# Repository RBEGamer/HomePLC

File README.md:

HomePLC is a PLC for smarthome purposes, to control your lamps, devices or machines. 
You can use as input several sensors or webservices. For the HomePLC you will need at least the main unit. 
The main unit contains a RaspberryPi witch run the HomePLC-Server software.
As connection to the modules (like relais, sensors,..), it uses a standard USB2RS485 stick.
To connect the Mainunit to the modules it uses a 4 wire standard cable, which contains power and serial data. 
The Serial data bus is RS485@9600 but you can change it to our needs.

# Features:
* RaspberryPi and Arduino based hardware
* PLC oriented programming node based programming language
* Simple Programming Interface
* Arduino Based Hardware Extentions (DMX, Relais, SensorInterfaces, Analog Inputs, GPS, RTC, RS485, PWM-Output,...)
* Webservice integration (OpenWeatherMap,Philips Hue, Netatmo)
* Din Rail Case for integration into exisitng PLC Systems
* Debug webserver at port 5555
* LUA scripting integration to create complex control flows and create your own programming nodes
* Simple Full-Duplex RS485 Protocol to connect further hardware
* Actor and sensor can be combined in one module

# HARDWARE (MAIN UNIT)
* Linux based computer, to mount it at the DIN-Rail i used a RaspberryPi 3
* 5V and 12V switching power supply (search for combined)
* Arduino Micro (for controlling system status: LED, LCD, POWER)
* I2C 16x2 Display for status information
* 3 LEDs for power, error and message signals
* Sub-D9 female connector to connect modules
* 2 USB2Serial converter, if your linux board have no gpio based serial port 
* RS485 transceiver chip [optional isolated]
* DIN-Rail case

# HARDWARE 4-DO (SAMPLE MODULE)
* Din-Rail case
* 2 state leds [optional]
* Arduino micro
* RS485 transceiver chip [optional isolated]
* 2 Sub-D9 female connectors [in/out]
* 4 channel relais board

# SOFTWARE
The software are splitted in two parts :
* HomePLC-Server (runs on your main unit to control your devices, this repo)
* HomePLC-Commander (Design the interaction beween the modules and create the schematic files and upload it to your main unit)

### The HomePLC_Commander software was moved to [HomePLC_Commander](https://github.com/RBEGamer/HomePLC_Commander)

###  SCHEMATIC

###  NODE PARAMETER EDITOR

The HomePLC schematic is a grafical control language (like FUP) to design the control logic.
You have several nodes like standard logical operations :
* AND, OR, NOT,...
* FLIPFLOS
* MATH
* CONSTANS
* Time/r Nodes
* Compares
* Serial IN/OUT
* TCP/UDP IN/OUT
* DMX send

All other currently implemented nodes are located at:
`./Documentation/Implmented Nodes.csv`

If you have designed a schematic, enter the ip to upload a xml design file to the HomePLC-MainUnit.
The main unit will restart and will start to execute the new schematic. 
You can see the process and errors over the debug interfache.

# LOCATIONS
* A debug build of the HomePLC-Server for the RaspberryPi3 is located at `/Source/BUILDS/BUILD_15_01_2016/`
* The source of the HomePLC-Server to build ith on your own system is located at `./Source/SmartSPS/`
* The HomePLC-Commander source is located at `./Source/SmartPLC_Commander/`
* Sample programs for the HomePLC-Commander are located at `./Documentation/SampleConfig/for_smartsps_commander/`
* Pictures of the MainUnit hardware are located at `./Documentation/Pictures/`

# TODO
* Add MODBUS-TCP
* Add realtime node debugging
* Add cmakelists

# IMAGES
###  BASE MAIN UNIT

### TWO EXTENTIONS (left 6 channel relais, right, 12 channel analog input)

### OPEN MAIN UNIT

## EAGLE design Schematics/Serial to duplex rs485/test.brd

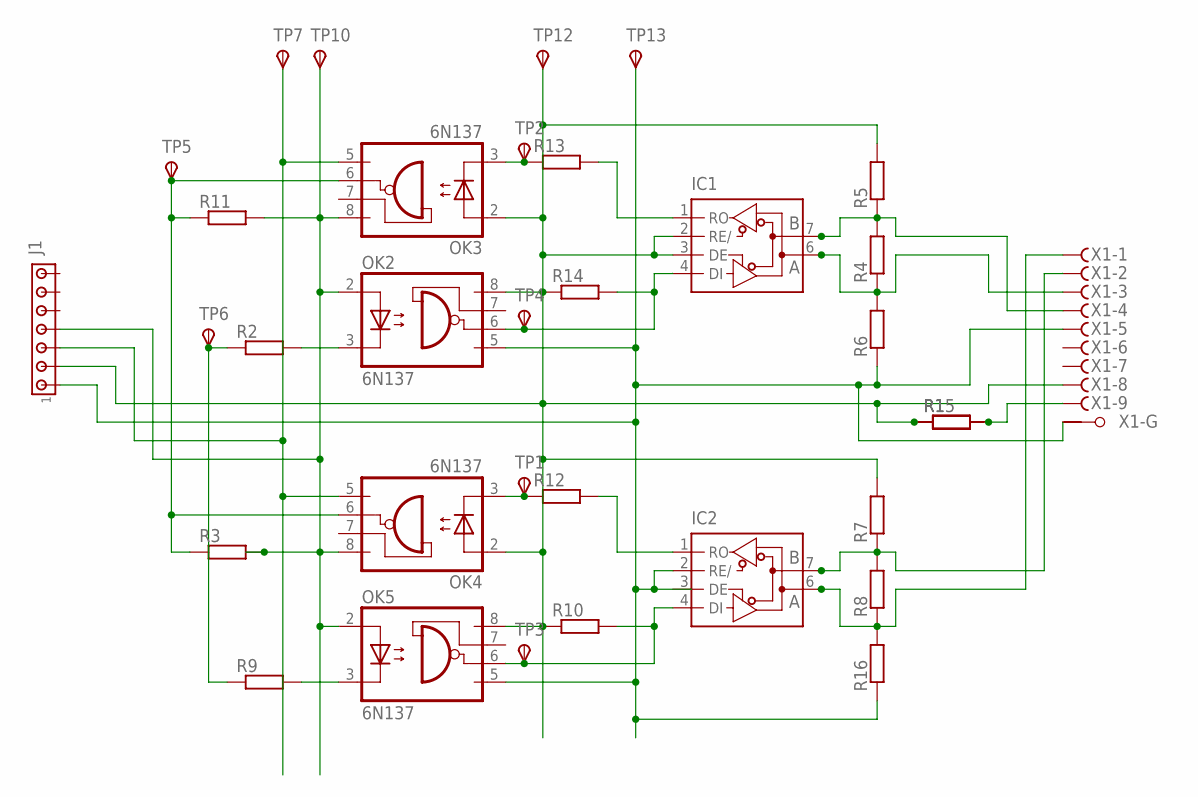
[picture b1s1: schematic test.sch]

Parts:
IC1, IC2: MAX481CSA; SO08
J1: MTA07-100; 10X07MTA
OK2, OK3, OK4, OK5: 6N137; DIL08
R1, R2, R3, R4, R5, R6, R7, R8, R9, R10, R11, R12, R13, R14, R15, R16: SMK
TP1, TP2, TP3, TP4, TP5, TP6, TP7, TP10, TP12, TP13: TPSB2,54; B2,54
X1: F09HPS; F09HP

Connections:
5VEXT: IC1.2 (RE/), IC1.3 (DE), J1.2, OK2.8 (VCC), OK3.2 (A), OK4.2 (A), OK5.8 (VCC), R1.2, R5.1, R7.1, R10.2, R14.2, R15.2, TP12.TP, X1.8 (F)
GND: IC1.5 (GND), IC2.5 (GND)
unnamed: IC1.7 (B), R4.1, R5.2, X1.4 (F)
unnamed: IC1.6 (A), R4.2, R6.1, X1.3 (F)
unnamed: IC2.7 (B), R7.2, R8.1, X1.2 (F)
unnamed: IC2.6 (A), R8.2, R16.1, X1.1 (F)
unnamed: OK3.3 (C), R13.2, TP2.TP
unnamed: IC1.1 (RO), R13.1
unnamed: OK5.3 (C), R9.1
unnamed: OK4.3 (C), R12.2, TP1.TP
unnamed: J1.3, OK3.5 (GND), OK4.5 (GND), TP7.TP
unnamed: R1.1, R15.1, X1.9 (F)
unnamed: IC2.4 (DI), OK5.6 (VO), R10.1, TP3.TP
unnamed: IC1.4 (DI), OK2.6 (VO), R14.1, TP4.TP
unnamed: OK2.3 (C), R2.1
unnamed: IC2.2 (RE/), J1.1, OK2.5 (GND), OK5.5 (GND), R6.2, R16.2, TP13.TP, X1.5 (F), X1.G1
unnamed: J1.4, OK2.2 (A), OK3.8 (VCC), OK4.8 (VCC), OK5.2 (A), R3.1, R11.1, TP10.TP
unnamed: R2.2, R9.2, TP6.TP
unnamed: OK3.6 (VO), OK4.6 (VO), R3.2, R11.2, TP5.TP
unnamed: IC2.1 (RO), R12.1
VCC: IC1.8 (VCC), IC2.8 (VCC)

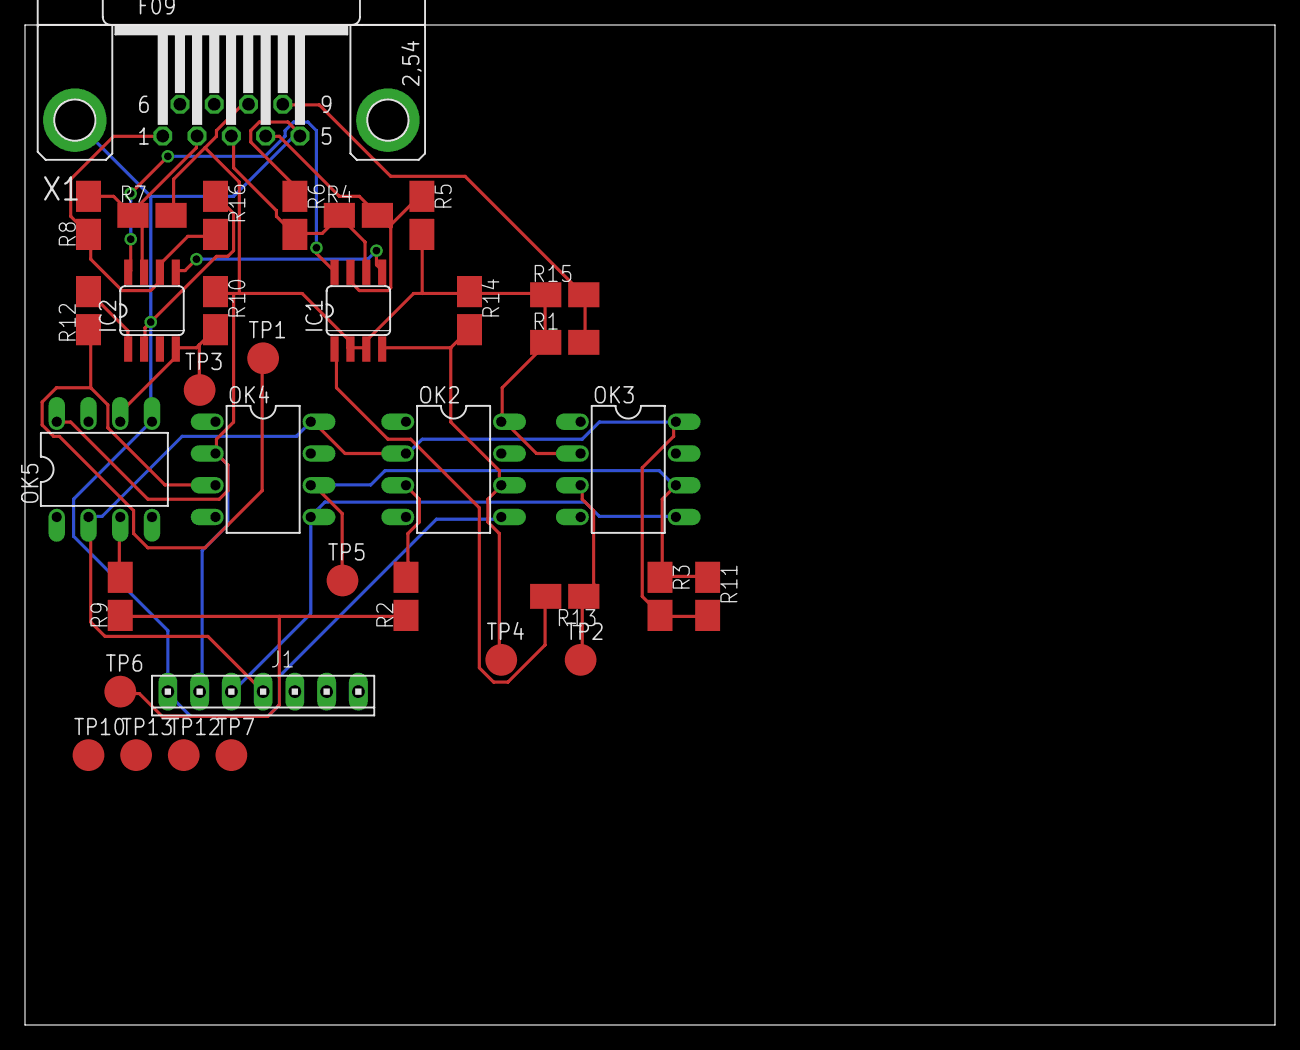
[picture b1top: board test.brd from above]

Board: 2 copper layers, 100.0 x 80.0 mm, 34 parts (0 on the bottom side), 21 nets.

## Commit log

2015-12-06 added some project files
2015-12-06 added 3d print files
2015-12-07 add all nodes from 06.12 to xml parse
2015-12-08 added basetimer node (not tested)
2015-12-08 fix floatcomp
2015-12-08 timer fix (not tested) int comp fix
2015-12-08 hue blinking with timer
2015-12-08 remove all node updates
2015-12-08 remove !="TRUE" 1.0f
2015-12-08 update only connected nodes if output has changed
2015-12-08 litte changes
2015-12-08 added implemented nodes list
2015-12-09 added socket downloading for schematic at startup
    downloads the latest schematic on startup from the :
    localhost:80/test.html
2015-12-09 added serial to s485 schematics
2015-12-09 added partlist for base
2015-12-09 added string operations
2015-12-10 node parsing bugfix
2015-12-10 added samples
2015-12-10 added som colors to excel list
2015-12-10 added CppDepend project
2015-12-10 del logs
2015-12-13 edited sample config
2015-12-13 strcomp fix
2015-12-14 added thread test
2015-12-14 debug haat server but protocol not finished
2015-12-14 working debug server
2015-12-14 added html colors and debug level html
2015-12-14 fixed html table
2015-12-14 added debug levels and request parsing
2015-12-14 small html fix
2015-12-14 added reload_schematic function with pointer check
2015-12-14 reload debug
2015-12-14 added mutex to read state
2015-12-14 on the fly reload test but server thread not still working
2015-12-14 working on the fly reload
2015-12-16 updated node list
2015-12-16 added webserver files
2015-12-16 remove bug in xls
2015-12-17 added use timer constructor
2015-12-17 added update(), in set_value functions
2015-12-17 nbdi use timer = false
2015-12-25 fixed missing registering cmd in extention code
2015-12-25 added one wire sketch
2015-12-25 added power led state to arduino sketches
2015-12-25 added temp pointer
2015-12-26 added c# programmer ui project
2015-12-26 added additional node loading
2015-12-26 added implemented nodes csv
2015-12-26 addede new csv and create dyn panel params loading (begin, test)
2015-12-26 working creating labels dynamicly
2015-12-26 added num up down test
2015-12-26 added extention name collum to csv
2015-12-26 csv openwathermap bugfix
2015-12-26 added paramerter load funcktion
2015-12-30 added eqro flush and tx enable at D3
2015-12-30 added flush and en tx to eowt
2015-12-31 added pictures
2015-12-31 added add/remove node btn
2015-12-31 added drawing timer
2016-01-01 added gdi drawing prototype
2016-01-01 added pos xml saving
2016-01-01 added clar all btn
2016-01-01 added headlinetext and connection descriptions
2016-01-01 added basic clipping
2016-01-01 int color fix
2016-01-01 added mouse dragable nodes
2016-01-01 added clickable connections
2016-01-01 added more clipping
2016-01-01 create connection pairs
2016-01-01 fist bezier curve
2016-01-01 added fix to connect twiche the same connectors
2016-01-02 added: doubleclick ojn a connection to remove all connections
2016-01-02 added saving connectionstring to xml
2016-01-02 fixed upload
    check if the lenght is right
2016-01-02 some cosmetics
2016-01-03 save schematic as file
2016-01-04 start with xml parsing
2016-01-04 start witg oarsing ndes
2016-01-04 added commander text xml
2016-01-06 added scoll sliders
2016-01-06 added protocol xlsx file
2016-01-11 multi schematic save
2016-01-11 loading schem final
2016-01-11 bugfixing save bug
2016-01-12 big mistake fix: call stack ._.
2016-01-12 commander: node clone bugfix
2016-01-12 added connection reconstruction
2016-01-14 string append bugfix
2016-01-14 removed from eqro the eqri auto response
2016-01-14 bugfic in 16x2 display sketch
2016-01-14 sime stuff
2016-01-14 added new build 14_01_2016
2016-01-15 added temperture node
2016-01-15 added change debug level
2016-01-16 more debug stuff
    +added temp schematic
    +bugfix in eowt
2016-01-16 added build 15_01_2015
2016-01-16 vorbereitung für serial nodes
2016-01-16 added experimental nbss
2016-01-16 added experimental nbrs
2016-01-16 added vs filter
2016-01-16 added missing delete
2016-01-17 added lua 5.3 files
2016-01-17 added the beginning of the lua node
2016-01-18 added basic lua script
2016-01-18 added node creator app
2016-01-21 parsinf more infos from xml imput
2016-01-21 added __FILE__ __LINE__ and filewrite
2016-01-21 added a __NO__FF__ define
2016-01-21 added more infos to xml export
2016-01-21 fix xml export
2016-01-22 experimental lua node
2016-01-30 added sockclose at request end
2016-12-10 removed sps commander to other repo
2017-03-01 Rename arduino_sketch_bnid_16x2.txt to arduino_sketch_bnid_16x2.ino
2017-03-01 Rename arduino_sketch_eowt.txt to arduino_sketch_eowt.ino
2017-03-01 Rename arduino_sketch_eqri.txt to arduino_sketch_eqri.ino
2017-03-01 Rename arduino_sketch_eqro.txt to arduino_sketch_eqro.ino
